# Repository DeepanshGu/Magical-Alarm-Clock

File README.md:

# Magical Alarm Clock

A custom-built alarm clock featuring an ST7789 display, XIAO ESP32-C3 microcontroller, 
4 physical buttons, and a buzzer — designed from scratch as part of Hack Club's 
[BLARE](https://blare.hackclub.com/) program.

Built entirely with KiCad (schematic + PCB), Fusion 360 (enclosure), and Arduino IDE (firmware).

## Features

- Real-time clock display on a 284x76 ST7789 TFT screen
- Set the current time manually using onboard buttons (fully offline — no WiFi/NTP required)
- Set, enable, and disable a daily alarm
- Buzzer sounds when the alarm triggers, silenced with a button press
- Fully custom 2-layer PCB — no breadboard or dev-kit shield required
- 3D-printable enclosure designed in Fusion 360

## Hardware

| Component | Notes |
|---|---|
| Seeed XIAO ESP32-C3 | Main microcontroller |
| ST7789 TFT Display | 284x76 resolution (unusual — not the standard 240x320) |
| 4x Push Buttons | Mode / Increment / Decrement / Alarm toggle |
| Buzzer | Alarm sound output |
| Custom PCB | 2-layer, designed in KiCad |

## Bill of Materials

| Part | Qty | Unit Price (USD) | Link | Notes |
| :--- | :---: | :---: | :--- | :--- |
| Seeed XIAO ESP32-C3 | 1 | $5.49 | [Seeed Studio](https://www.seeedstudio.com/XIAO-ESP32C3-p-5431.html) | Main microcontroller |
| 2.25" TFT 76x284 SPI Display (ST7789P3) | 1 | $2.50 | [BuyDisplay](https://www.buydisplay.com/chinese/2-25-inch-tft-serial-spi-76x284-lcd-display-module-w-st7789p3) | Non-standard resolution match |
| Tactile Push Button Switch 6x6mm (pack of 20) | 1 | $2.50 | [Adafruit](https://www.adafruit.com/product/367) | Only 4 needed per clock; pack covers spares |
| 5V Piezo Buzzer | 1 | $0.95 | [Adafruit](https://www.adafruit.com/products/1536) | Breadboard-friendly; no driver circuit needed |
| M3 Brass Heat-Set Inserts (pack of 50) | 1 | $5.95 | [Adafruit](https://www.adafruit.com/product/4256) | Only 4 needed per clock; pack covers spares |
| M3 Screws (6-8mm length) | 4 | ~$0.10 each | — | Widely available individually at hardware store |
| Custom PCB | 1 | ~$8.20 (for 5) | — | JLCPCB quote for 2-layer 75x107mm board |
| **Total Estimated Cost** | — | **~$25.99** | — | **Includes single-unit parts & bulk packs/PCBs** |

## Repository Structure

## Building the PCB

1. Open the KiCad project files in the `/pcb` folder.
2. Gerber and drill files are included for direct upload to a fabrication service (e.g. JLCPCB).
3. Board is a standard 2-layer FR-4 PCB.

## Firmware Setup

1. Install [Arduino IDE](https://www.arduino.cc/en/software).
2. Add ESP32 board support via Boards Manager.
3. Install these libraries via Library Manager:
   - `Adafruit ST7735 and ST7789`
   - `Adafruit GFX`
4. Open `/firmware/magical_alarm_clock.ino`.
5. Update the GPIO pin definitions at the top of the file to match your wiring.
6. Select **XIAO_ESP32C3** as the board, choose the correct COM port, and upload.

## Enclosure

The case was designed in Fusion 360 around the PCB and display's real dimensions, 
with support posts for heat-set inserts and a cutout for the display and buttons. 
STEP files are available in `/enclosure`.

## Credits

- Built following the [BLARE](https://blare.hackclub.com/) guide by Liam Newbill, part of Hack Club's Stardance program.
- Designed and built by [Deepansh Gupta](https://github.com/DeepanshGu).

## License

*No license added yet.*

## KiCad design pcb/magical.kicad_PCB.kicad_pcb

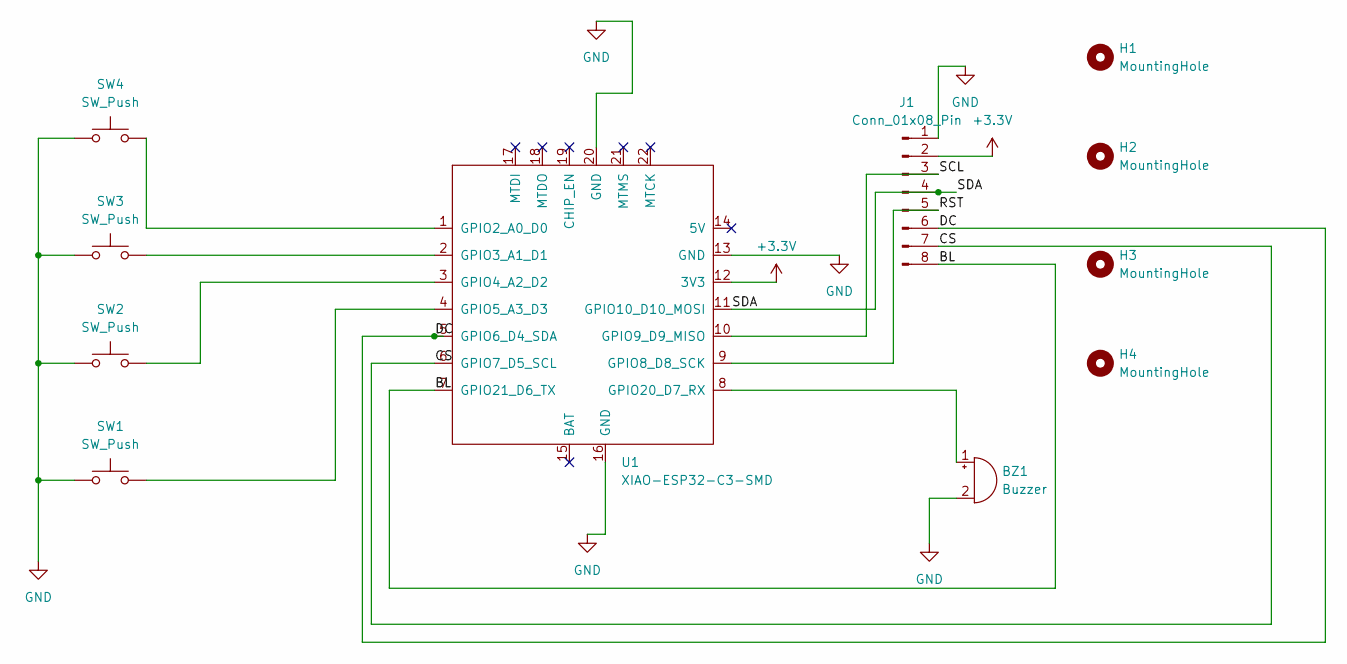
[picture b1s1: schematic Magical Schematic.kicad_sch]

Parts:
BZ1: Buzzer; Buzzer_12x9.5RM7.6
H1, H2, H3, H4: MountingHole; MountingHole_3.2mm_M3
J1: Conn_01x08_Pin; PinSocket_1x08_P2.54mm_Vertical
SW1, SW2, SW3, SW4: SW_Push; SW_Cherry_MX_1.00u_PCB
U1: XIAO-ESP32-C3-SMD; MCU_Seeed_ESP32C3

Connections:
+3.3V: J1.2, U1.12 (3V3)
/BL: J1.8, U1.7 (GPIO21_D6_TX)
/CS: J1.7, U1.6 (GPIO7_D5_SCL)
/DC: J1.6, U1.5 (GPIO6_D4_SDA)
/RST: J1.5, U1.9 (GPIO8_D8_SCK)
/SCL: J1.3, U1.10 (GPIO9_D9_MISO)
/SDA: J1.4, U1.11 (GPIO10_D10_MOSI)
GND: BZ1.2 (-), J1.1, SW1.1, SW2.1, SW3.1, SW4.1, U1.13 (GND), U1.16 (GND), U1.20 (GND)
unnamed: BZ1.1 (+), U1.8 (GPIO20_D7_RX)
unnamed: SW4.2, U1.1 (GPIO2_A0_D0)
unnamed: SW3.2, U1.2 (GPIO3_A1_D1)
unnamed: SW2.2, U1.3 (GPIO4_A2_D2)
unnamed: SW1.2, U1.4 (GPIO5_A3_D3)

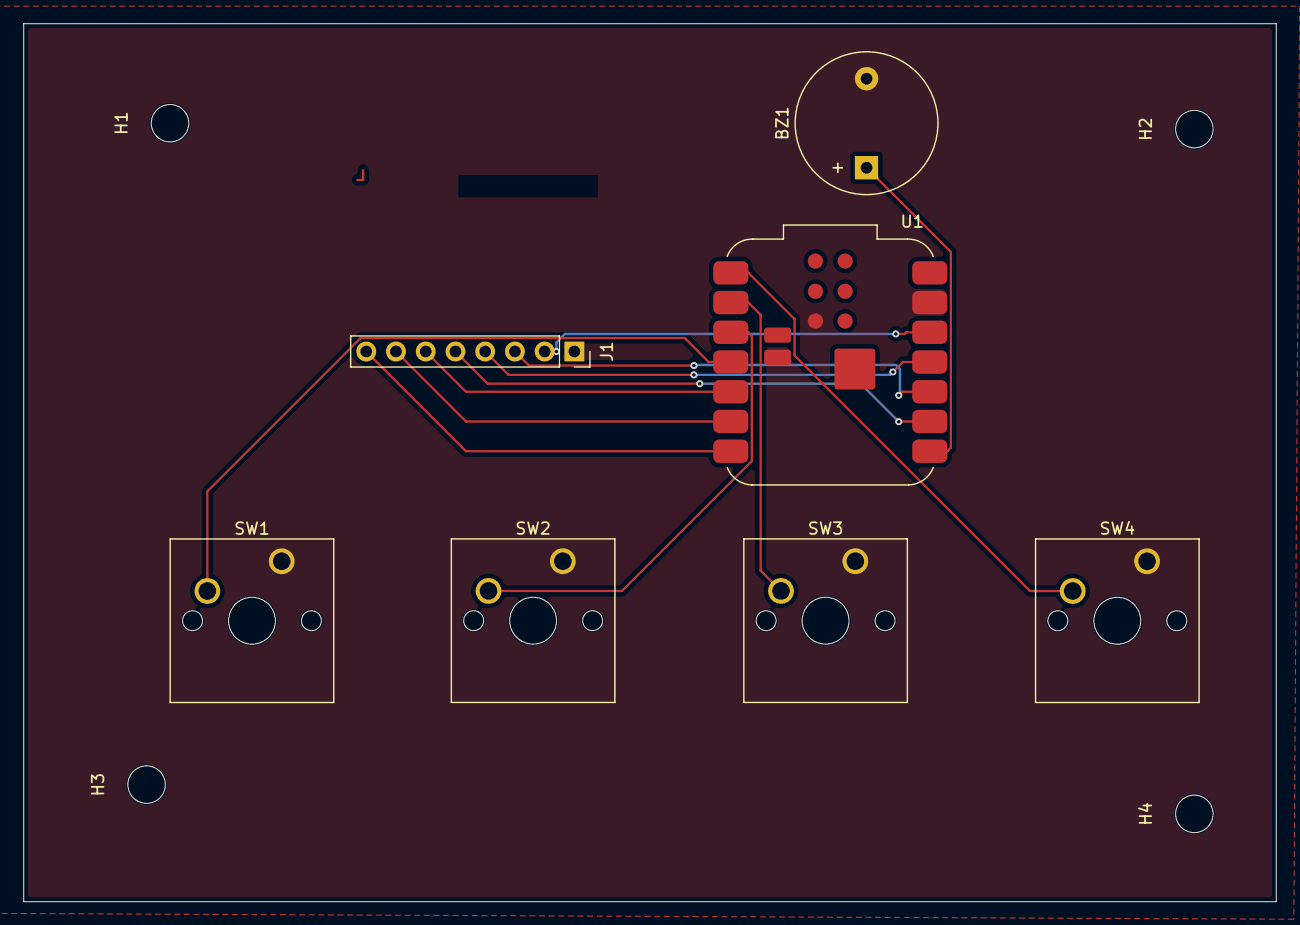
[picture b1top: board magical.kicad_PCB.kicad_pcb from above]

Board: 2 copper layers, 107.0 x 75.0 mm, 11 parts (0 on the bottom side), 13 nets.
